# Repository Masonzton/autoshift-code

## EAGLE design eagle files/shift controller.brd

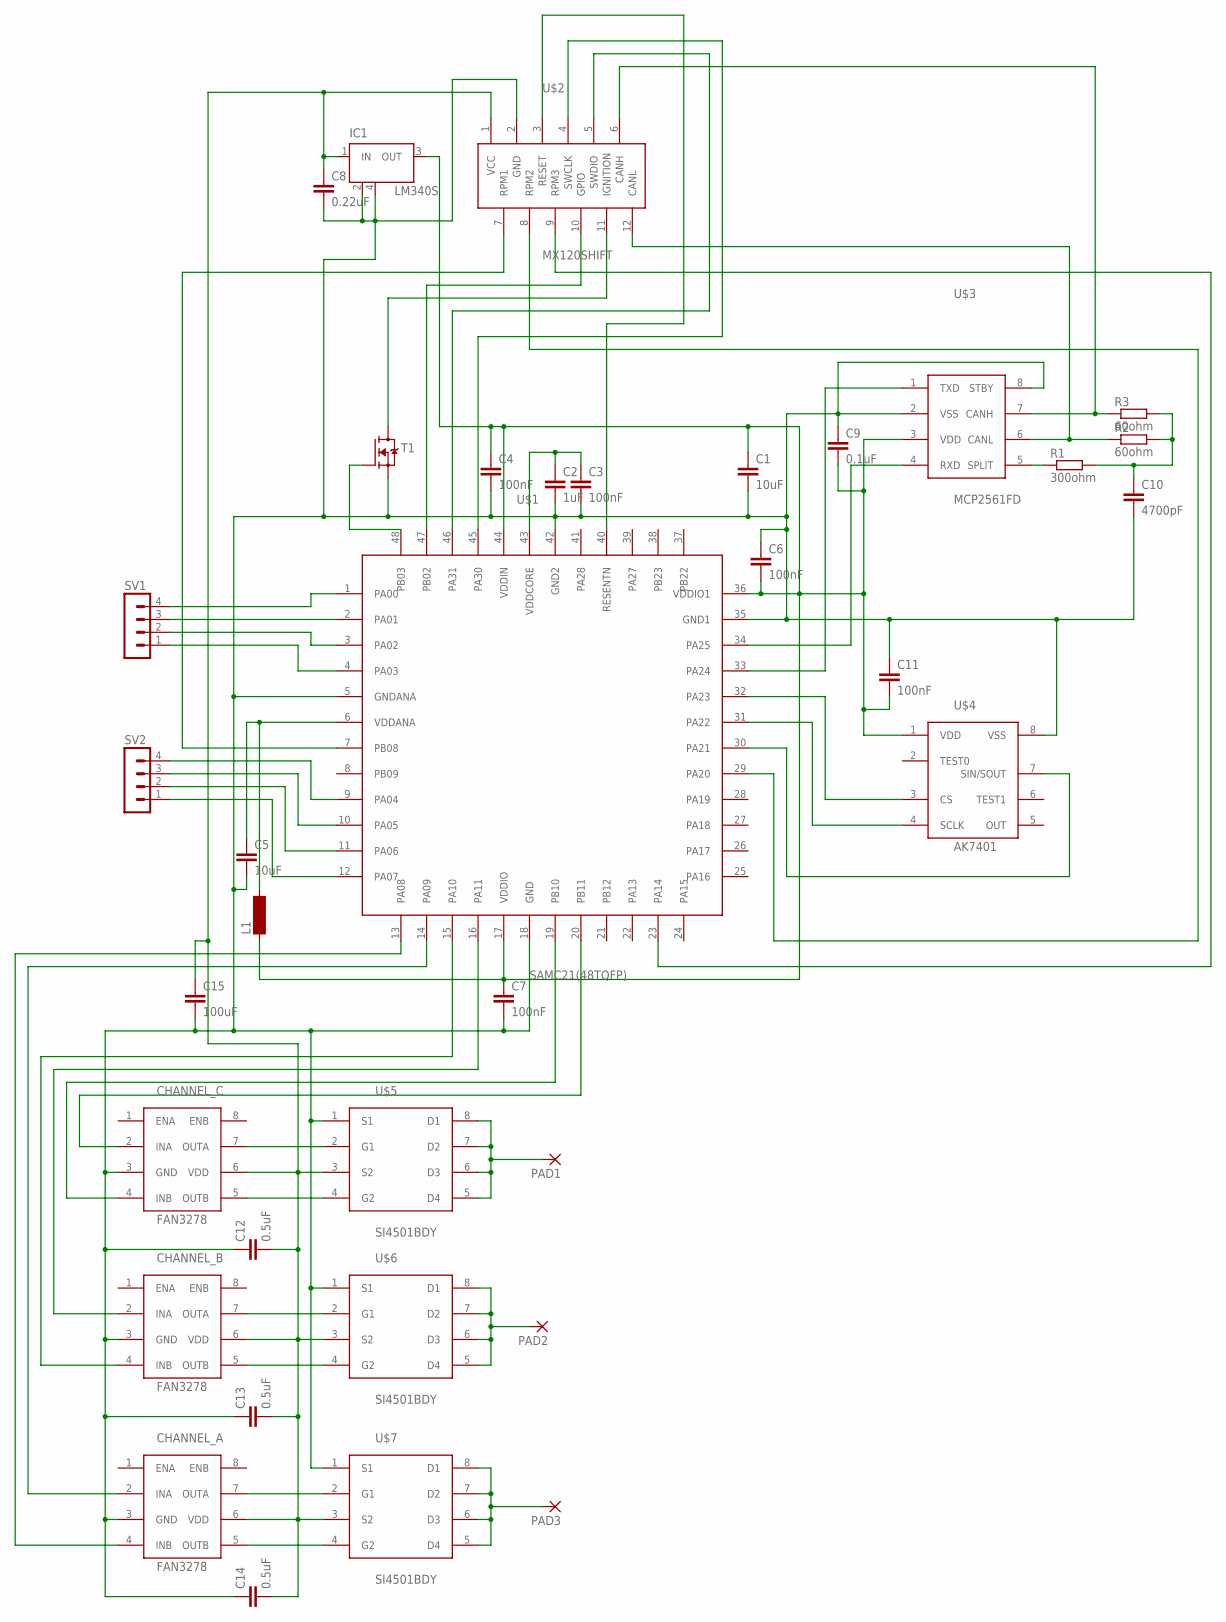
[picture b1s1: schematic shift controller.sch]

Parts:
C1, C5: 10uF; C1206
C2: 1uF; C1206
C3, C4, C6, C7, C11: 100nF; C1206
C8: 0.22uF; C1206
C9: 0.1uF; C1206
C10: 4700pF; C1206
C12, C13, C14: 0.5uF; C1206
C15: 100uF; C2.5-5
CHANNEL_A: FAN3278; SOIC-8
CHANNEL_B: FAN3278; SOIC-8
CHANNEL_C: FAN3278; SOIC-8
IC1: LM340S; SOT223
L1: SM-1206
PAD1, PAD2, PAD3: 3,81/1,4
R1: 300ohm; R1206
R2, R3: 60ohm; R1206
SV1, SV2: MA04-1
T1: MOSFET-N-SOT223; SOT223
U$1: SAMC21(48TQFP); TQFP-48
U$2: MX120SHIFT; 12X3.5PITCH
U$3: MCP2561FD; SOIC-8
U$4: AK7401; SOIC-8
U$5, U$6, U$7: SI4501BDY; SOIC-8

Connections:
unnamed: U$1.45 (PA30), U$2.4 (SWCLK)
unnamed: U$1.46 (PA31), U$2.5 (SWDIO)
unnamed: U$1.34 (PA25), U$3.4 (RXD)
unnamed: U$1.33 (PA24), U$3.1 (TXD)
unnamed: R3.1, U$2.6 (CANH), U$3.7 (CANH)
unnamed: R2.1, U$2.12 (CANL), U$3.6 (CANL)
unnamed: U$1.40 (RESENTN), U$2.3 (RESET)
unnamed: U$1.7 (PB08), U$2.7 (RPM1)
unnamed: U$1.23 (PA14), U$2.9 (RPM3)
unnamed: U$1.29 (PA20), U$2.8 (RPM2)
unnamed: SV1.4, U$1.1 (PA00)
unnamed: C8.1, C12.2, C13.2, C14.2, C15.1, CHANNEL_A.6 (VDD), CHANNEL_B.6 (VDD), CHANNEL_C.6 (VDD), IC1.1 (IN), U$2.1 (VCC), U$5.3 (S2), U$6.3 (S2), U$7.3 (S2)
unnamed: C1.1, C4.1, C6.2, C7.1, C9.2, C11.2, IC1.3 (OUT), L1.1, U$1.17 (VDDIO), U$1.36 (VDDIO1), U$1.44 (VDDIN), U$3.3 (VDD), U$4.1 (VDD)
unnamed: C2.1, C3.1, U$1.43 (VDDCORE)
unnamed: C5.1, L1.2, U$1.6 (VDDANA)
unnamed: R1.1, U$3.5 (SPLIT)
unnamed: C10.1, R1.2, R2.2, R3.2
unnamed: CHANNEL_C.2 (INA), U$1.20 (PB11)
unnamed: U$1.30 (PA21), U$4.7 (SIN/SOUT)
unnamed: U$1.31 (PA22), U$4.4 (SCLK)
unnamed: U$1.32 (PA23), U$4.3 (CS)
unnamed: T1.2 (D), T1.4 (D), U$2.11 (IGNITION)
unnamed: T1.1 (G), U$1.48 (PB03)
unnamed: PAD1.1, U$5.5 (D4), U$5.6 (D3), U$5.7 (D2), U$5.8 (D1)
unnamed: PAD2.1, U$6.5 (D4), U$6.6 (D3), U$6.7 (D2), U$6.8 (D1)
unnamed: PAD3.1, U$7.5 (D4), U$7.6 (D3), U$7.7 (D2), U$7.8 (D1)
unnamed: CHANNEL_C.4 (INB), U$1.19 (PB10)
unnamed: CHANNEL_C.7 (OUTA), U$5.2 (G1)
unnamed: CHANNEL_C.5 (OUTB), U$5.4 (G2)
unnamed: CHANNEL_B.7 (OUTA), U$6.2 (G1)
unnamed: CHANNEL_B.5 (OUTB), U$6.4 (G2)
unnamed: CHANNEL_A.7 (OUTA), U$7.2 (G1)
unnamed: CHANNEL_A.5 (OUTB), U$7.4 (G2)
unnamed: C1.2, C2.2, C3.2, C4.2, C5.2, C6.1, C7.2, C8.2, C9.1, C10.2, C11.1, C12.1, C13.1, C14.1, C15.2, CHANNEL_A.3 (GND), CHANNEL_B.3 (GND), CHANNEL_C.3 (GND), IC1.2 (GND), IC1.4 (GND), T1.3 (S), U$1.5 (GNDANA), U$1.18 (GND), U$1.35 (GND1), U$1.42 (GND2), U$2.2 (GND), U$3.2 (VSS), U$3.8 (STBY), U$4.8 (VSS), U$5.1 (S1), U$6.1 (S1), U$7.1 (S1)
unnamed: CHANNEL_B.2 (INA), U$1.16 (PA11)
unnamed: CHANNEL_B.4 (INB), U$1.15 (PA10)
unnamed: CHANNEL_A.2 (INA), U$1.14 (PA09)
unnamed: CHANNEL_A.4 (INB), U$1.13 (PA08)
unnamed: U$1.47 (PB02), U$2.10 (GPIO)
unnamed: SV1.3, U$1.2 (PA01)
unnamed: SV1.2, U$1.3 (PA02)
unnamed: SV1.1, U$1.4 (PA03)
unnamed: SV2.4, U$1.9 (PA04)
unnamed: SV2.3, U$1.10 (PA05)
unnamed: SV2.2, U$1.11 (PA06)
unnamed: SV2.1, U$1.12 (PA07)

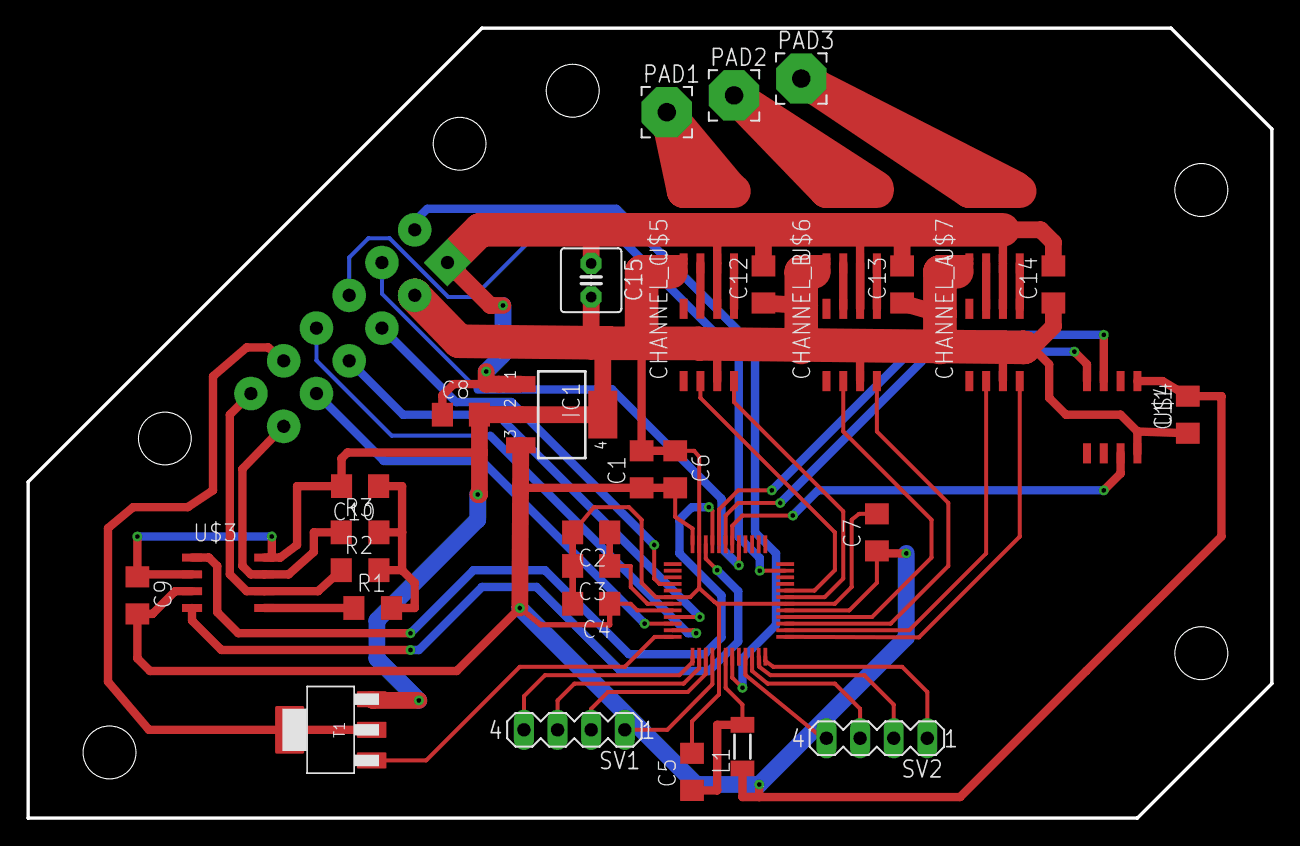
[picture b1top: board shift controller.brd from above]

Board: 2 copper layers, 94.0 x 59.7 mm, 36 parts (0 on the bottom side), 46 nets.

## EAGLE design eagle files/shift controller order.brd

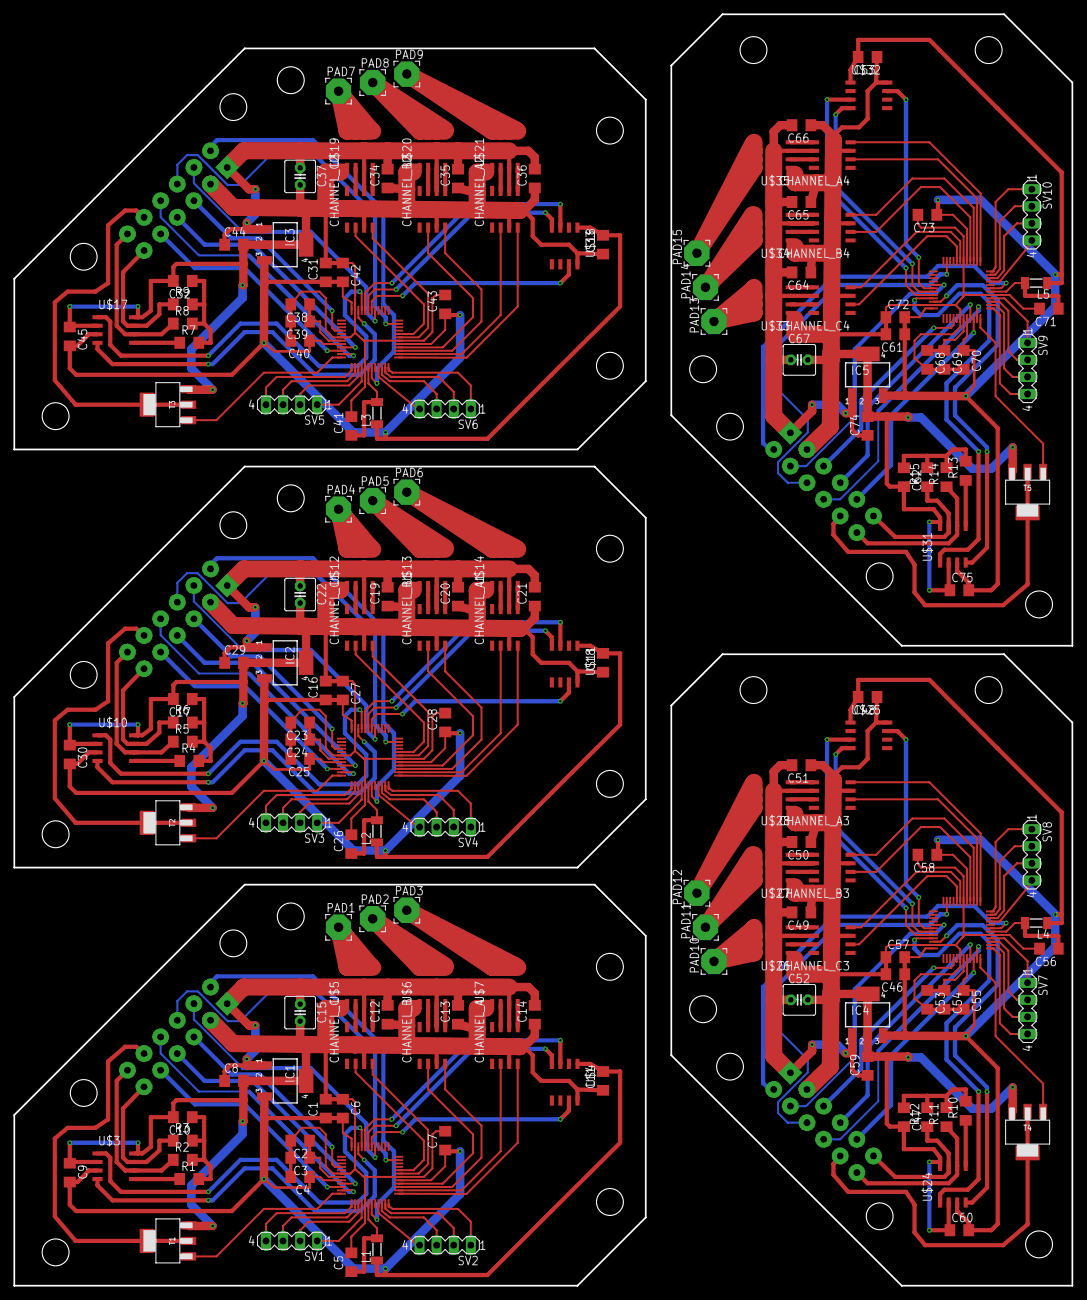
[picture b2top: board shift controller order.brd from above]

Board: 2 copper layers, 157.5 x 189.2 mm, 180 parts (0 on the bottom side), 230 nets.

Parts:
C1, C5, C16, C26, C31, C41, C46, C56, C61, C71: 10uF; C1206
C2, C23, C38, C53, C68: 1uF; C1206
C3, C4, C6, C7, C11, C18, C24, C25, C27, C28, C33, C39, C40, C42, C43, C48, C54, C55, C57, C58, C63, C69, C70, C72, C73: 100nF; C1206
C8, C29, C44, C59, C74: 0.22uF; C1206
C9, C30, C45, C60, C75: 0.1uF; C1206
C10, C17, C32, C47, C62: 4700pF; C1206
C12, C13, C14, C19, C20, C21, C34, C35, C36, C49, C50, C51, C64, C65, C66: 0.5uF; C1206
C15, C22, C37, C52, C67: 100uF; C2.5-5
CHANNEL_A, CHANNEL_A1, CHANNEL_A2, CHANNEL_A3, CHANNEL_A4: FAN3278; SOIC-8
CHANNEL_B, CHANNEL_B1, CHANNEL_B2, CHANNEL_B3, CHANNEL_B4: FAN3278; SOIC-8
CHANNEL_C, CHANNEL_C1, CHANNEL_C2, CHANNEL_C3, CHANNEL_C4: FAN3278; SOIC-8
IC1, IC2, IC3, IC4, IC5: LM340S; SOT223
L1, L2, L3, L4, L5: SM-1206
PAD1, PAD2, PAD3, PAD4, PAD5, PAD6, PAD7, PAD8, PAD9, PAD10, PAD11, PAD12, PAD13, PAD14, PAD15: 3,81/1,4
R1, R4, R7, R10, R13: 300ohm; R1206
R2, R3, R5, R6, R8, R9, R11, R12, R14, R15: 60ohm; R1206
SV1, SV2, SV3, SV4, SV5, SV6, SV7, SV8, SV9, SV10: MA04-1
T1, T2, T3, T4, T5: SOT223
U$1, U$8, U$15, U$22, U$29: SAMC21(48TQFP); TQFP-48
U$2, U$9, U$16, U$23, U$30: MX120SHIFT; 12X3.5PITCH
U$3, U$10, U$17, U$24, U$31: MCP2561FD; SOIC-8
U$4, U$11, U$18, U$25, U$32: AK7401; SOIC-8
U$5, U$6, U$7, U$12, U$13, U$14, U$19, U$20, U$21, U$26, U$27, U$28, U$33, U$34, U$35: SI4501BDY; SOIC-8

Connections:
unnamed: U$1.45, U$2.4
unnamed: U$1.46, U$2.5
unnamed: U$1.34, U$3.4
unnamed: U$1.33, U$3.1
unnamed: R3.1, U$2.6, U$3.7
unnamed: R2.1, U$2.12, U$3.6
unnamed: U$1.40, U$2.3
unnamed: U$1.7, U$2.7
unnamed: U$1.23, U$2.9
unnamed: U$1.29, U$2.8
unnamed: SV1.4, U$1.1
unnamed: C8.1, C12.2, C13.2, C14.2, C15.1, CHANNEL_A.6, CHANNEL_B.6, CHANNEL_C.6, IC1.1, U$2.1, U$5.3, U$6.3, U$7.3
unnamed: C1.1, C4.1, C6.2, C7.1, C9.2, C11.2, IC1.3, L1.1, U$1.17, U$1.36, U$1.44, U$3.3, U$4.1
unnamed: C2.1, C3.1, U$1.43
unnamed: C5.1, L1.2, U$1.6
unnamed: R1.1, U$3.5
unnamed: C10.1, R1.2, R2.2, R3.2
unnamed: CHANNEL_C.2, U$1.20
unnamed: U$1.30, U$4.7
unnamed: U$1.31, U$4.4
unnamed: U$1.32, U$4.3
unnamed: T1.2, T1.4, U$2.11
unnamed: T1.1, U$1.48
unnamed: PAD1.1, U$5.5, U$5.6, U$5.7, U$5.8
unnamed: PAD2.1, U$6.5, U$6.6, U$6.7, U$6.8
unnamed: PAD3.1, U$7.5, U$7.6, U$7.7, U$7.8
unnamed: CHANNEL_C.4, U$1.19
unnamed: CHANNEL_C.7, U$5.2
unnamed: CHANNEL_C.5, U$5.4
unnamed: CHANNEL_B.7, U$6.2
unnamed: CHANNEL_B.5, U$6.4
unnamed: CHANNEL_A.7, U$7.2
unnamed: CHANNEL_A.5, U$7.4
unnamed: C1.2, C2.2, C3.2, C4.2, C5.2, C6.1, C7.2, C8.2, C9.1, C10.2, C11.1, C12.1, C13.1, C14.1, C15.2, CHANNEL_A.3, CHANNEL_B.3, CHANNEL_C.3, IC1.2, IC1.4, T1.3, U$1.5, U$1.18, U$1.35, U$1.42, U$2.2, U$3.2, U$3.8, U$4.8, U$5.1, U$6.1, U$7.1
unnamed: CHANNEL_B.2, U$1.16
unnamed: CHANNEL_B.4, U$1.15
unnamed: CHANNEL_A.2, U$1.14
unnamed: CHANNEL_A.4, U$1.13
unnamed: U$1.47, U$2.10
unnamed: SV1.3, U$1.2
unnamed: SV1.2, U$1.3
unnamed: SV1.1, U$1.4
unnamed: SV2.4, U$1.9
unnamed: SV2.3, U$1.10
unnamed: SV2.2, U$1.11
unnamed: SV2.1, U$1.12
unnamed: U$8.45, U$9.4
unnamed: U$8.46, U$9.5
unnamed: U$8.33, U$10.1
unnamed: R6.1, U$9.6, U$10.7
unnamed: R5.1, U$9.12, U$10.6
unnamed: U$8.40, U$9.3
unnamed: C16.1, C18.2, C25.1, C27.2, C28.1, C30.2, IC2.3, L2.1, U$8.17, U$8.36, U$8.44, U$10.3, U$11.1
unnamed: C23.1, C24.1, U$8.43
unnamed: C26.1, L2.2, U$8.6
unnamed: U$8.34, U$10.4
unnamed: R4.1, U$10.5
unnamed: C17.1, R4.2, R5.2, R6.2
unnamed: U$8.30, U$11.7
unnamed: U$8.31, U$11.4
unnamed: U$8.32, U$11.3
unnamed: T2.2, T2.4, U$9.11
unnamed: T2.1, U$8.48
unnamed: PAD4.1, U$12.5, U$12.6, U$12.7, U$12.8
unnamed: PAD5.1, U$13.5, U$13.6, U$13.7, U$13.8
unnamed: PAD6.1, U$14.5, U$14.6, U$14.7, U$14.8
unnamed: C19.2, C20.2, C21.2, C22.1, C29.1, CHANNEL_A1.6, CHANNEL_B1.6, CHANNEL_C1.6, IC2.1, U$9.1, U$12.3, U$13.3, U$14.3
unnamed: CHANNEL_C1.7, U$12.2
unnamed: CHANNEL_C1.5, U$12.4
unnamed: CHANNEL_B1.7, U$13.2
unnamed: CHANNEL_B1.5, U$13.4
unnamed: CHANNEL_A1.7, U$14.2
unnamed: CHANNEL_A1.5, U$14.4
unnamed: CHANNEL_C1.2, U$8.20
unnamed: CHANNEL_C1.4, U$8.19
unnamed: CHANNEL_B1.2, U$8.16
unnamed: CHANNEL_B1.4, U$8.15
unnamed: CHANNEL_A1.2, U$8.14
unnamed: CHANNEL_A1.4, U$8.13
unnamed: U$8.7, U$9.7
unnamed: U$8.23, U$9.9
unnamed: U$8.29, U$9.8
unnamed: U$8.47, U$9.10
unnamed: SV3.4, U$8.1
unnamed: SV3.3, U$8.2
unnamed: SV3.2, U$8.3
unnamed: SV3.1, U$8.4
unnamed: SV4.4, U$8.9
unnamed: SV4.3, U$8.10
unnamed: SV4.2, U$8.11
unnamed: SV4.1, U$8.12
unnamed: C16.2, C17.2, C18.1, C19.1, C20.1, C21.1, C22.2, C23.2, C24.2, C25.2, C26.2, C27.1, C28.2, C29.2, C30.1, CHANNEL_A1.3, CHANNEL_B1.3, CHANNEL_C1.3, IC2.2, IC2.4, T2.3, U$8.5, U$8.18, U$8.35, U$8.42, U$9.2, U$10.2, U$10.8, U$11.8, U$12.1, U$13.1, U$14.1
unnamed: U$15.45, U$16.4
unnamed: U$15.46, U$16.5
unnamed: U$15.33, U$17.1
unnamed: R9.1, U$16.6, U$17.7
unnamed: R8.1, U$16.12, U$17.6
unnamed: U$15.40, U$16.3
unnamed: C31.1, C33.2, C40.1, C42.2, C43.1, C45.2, IC3.3, L3.1, U$15.17, U$15.36, U$15.44, U$17.3, U$18.1
unnamed: C38.1, C39.1, U$15.43
unnamed: C41.1, L3.2, U$15.6
unnamed: U$15.34, U$17.4
unnamed: R7.1, U$17.5
unnamed: C32.1, R7.2, R8.2, R9.2
unnamed: U$15.30, U$18.7
unnamed: U$15.31, U$18.4
unnamed: U$15.32, U$18.3
unnamed: T3.2, T3.4, U$16.11
unnamed: T3.1, U$15.48
unnamed: PAD7.1, U$19.5, U$19.6, U$19.7, U$19.8
unnamed: PAD8.1, U$20.5, U$20.6, U$20.7, U$20.8
unnamed: PAD9.1, U$21.5, U$21.6, U$21.7, U$21.8
unnamed: C34.2, C35.2, C36.2, C37.1, C44.1, CHANNEL_A2.6, CHANNEL_B2.6, CHANNEL_C2.6, IC3.1, U$16.1, U$19.3, U$20.3, U$21.3
unnamed: CHANNEL_C2.7, U$19.2
unnamed: CHANNEL_C2.5, U$19.4
unnamed: CHANNEL_B2.7, U$20.2
unnamed: CHANNEL_B2.5, U$20.4
unnamed: CHANNEL_A2.7, U$21.2
unnamed: CHANNEL_A2.5, U$21.4
unnamed: CHANNEL_C2.2, U$15.20
unnamed: CHANNEL_C2.4, U$15.19
unnamed: CHANNEL_B2.2, U$15.16
unnamed: CHANNEL_B2.4, U$15.15
unnamed: CHANNEL_A2.2, U$15.14
unnamed: CHANNEL_A2.4, U$15.13
unnamed: U$15.7, U$16.7
unnamed: U$15.23, U$16.9
unnamed: U$15.29, U$16.8
unnamed: U$15.47, U$16.10
unnamed: SV5.4, U$15.1
unnamed: SV5.3, U$15.2
unnamed: SV5.2, U$15.3
unnamed: SV5.1, U$15.4
unnamed: SV6.4, U$15.9
unnamed: SV6.3, U$15.10
unnamed: SV6.2, U$15.11
unnamed: SV6.1, U$15.12
unnamed: C31.2, C32.2, C33.1, C34.1, C35.1, C36.1, C37.2, C38.2, C39.2, C40.2, C41.2, C42.1, C43.2, C44.2, C45.1, CHANNEL_A2.3, CHANNEL_B2.3, CHANNEL_C2.3, IC3.2, IC3.4, T3.3, U$15.5, U$15.18, U$15.35, U$15.42, U$16.2, U$17.2, U$17.8, U$18.8, U$19.1, U$20.1, U$21.1
unnamed: U$22.45, U$23.4
unnamed: U$22.46, U$23.5
unnamed: U$22.33, U$24.1
unnamed: R12.1, U$23.6, U$24.7
unnamed: R11.1, U$23.12, U$24.6
unnamed: U$22.40, U$23.3
unnamed: C46.1, C48.2, C55.1, C57.2, C58.1, C60.2, IC4.3, L4.1, U$22.17, U$22.36, U$22.44, U$24.3, U$25.1
unnamed: C53.1, C54.1, U$22.43
unnamed: C56.1, L4.2, U$22.6
unnamed: U$22.34, U$24.4
unnamed: R10.1, U$24.5
unnamed: C47.1, R10.2, R11.2, R12.2
unnamed: U$22.30, U$25.7
unnamed: U$22.31, U$25.4
unnamed: U$22.32, U$25.3
unnamed: T4.2, T4.4, U$23.11
unnamed: T4.1, U$22.48
unnamed: PAD10.1, U$26.5, U$26.6, U$26.7, U$26.8
unnamed: PAD11.1, U$27.5, U$27.6, U$27.7, U$27.8
unnamed: PAD12.1, U$28.5, U$28.6, U$28.7, U$28.8
unnamed: C49.2, C50.2, C51.2, C52.1, C59.1, CHANNEL_A3.6, CHANNEL_B3.6, CHANNEL_C3.6, IC4.1, U$23.1, U$26.3, U$27.3, U$28.3
unnamed: CHANNEL_C3.7, U$26.2
unnamed: CHANNEL_C3.5, U$26.4
unnamed: CHANNEL_B3.7, U$27.2
unnamed: CHANNEL_B3.5, U$27.4
unnamed: CHANNEL_A3.7, U$28.2
unnamed: CHANNEL_A3.5, U$28.4
unnamed: CHANNEL_C3.2, U$22.20
unnamed: CHANNEL_C3.4, U$22.19
unnamed: CHANNEL_B3.2, U$22.16
unnamed: CHANNEL_B3.4, U$22.15
unnamed: CHANNEL_A3.2, U$22.14
unnamed: CHANNEL_A3.4, U$22.13
unnamed: U$22.7, U$23.7
unnamed: U$22.23, U$23.9
unnamed: U$22.29, U$23.8
unnamed: U$22.47, U$23.10
unnamed: SV7.4, U$22.1
unnamed: SV7.3, U$22.2
unnamed: SV7.2, U$22.3
unnamed: SV7.1, U$22.4
unnamed: SV8.4, U$22.9
unnamed: SV8.3, U$22.10
unnamed: SV8.2, U$22.11
unnamed: SV8.1, U$22.12
unnamed: C46.2, C47.2, C48.1, C49.1, C50.1, C51.1, C52.2, C53.2, C54.2, C55.2, C56.2, C57.1, C58.2, C59.2, C60.1, CHANNEL_A3.3, CHANNEL_B3.3, CHANNEL_C3.3, IC4.2, IC4.4, T4.3, U$22.5, U$22.18, U$22.35, U$22.42, U$23.2, U$24.2, U$24.8, U$25.8, U$26.1, U$27.1, U$28.1
unnamed: U$29.45, U$30.4
unnamed: U$29.46, U$30.5
unnamed: U$29.33, U$31.1
unnamed: R15.1, U$30.6, U$31.7
unnamed: R14.1, U$30.12, U$31.6
unnamed: U$29.40, U$30.3
unnamed: C61.1, C63.2, C70.1, C72.2, C73.1, C75.2, IC5.3, L5.1, U$29.17, U$29.36, U$29.44, U$31.3, U$32.1
unnamed: C68.1, C69.1, U$29.43
unnamed: C71.1, L5.2, U$29.6
unnamed: U$29.34, U$31.4
unnamed: R13.1, U$31.5
unnamed: C62.1, R13.2, R14.2, R15.2
unnamed: U$29.30, U$32.7
unnamed: U$29.31, U$32.4
unnamed: U$29.32, U$32.3
unnamed: T5.2, T5.4, U$30.11
unnamed: T5.1, U$29.48
unnamed: PAD13.1, U$33.5, U$33.6, U$33.7, U$33.8
unnamed: PAD14.1, U$34.5, U$34.6, U$34.7, U$34.8
unnamed: PAD15.1, U$35.5, U$35.6, U$35.7, U$35.8
unnamed: C64.2, C65.2, C66.2, C67.1, C74.1, CHANNEL_A4.6, CHANNEL_B4.6, CHANNEL_C4.6, IC5.1, U$30.1, U$33.3, U$34.3, U$35.3
unnamed: CHANNEL_C4.7, U$33.2
unnamed: CHANNEL_C4.5, U$33.4
unnamed: CHANNEL_B4.7, U$34.2
unnamed: CHANNEL_B4.5, U$34.4
unnamed: CHANNEL_A4.7, U$35.2
unnamed: CHANNEL_A4.5, U$35.4
unnamed: CHANNEL_C4.2, U$29.20
unnamed: CHANNEL_C4.4, U$29.19
unnamed: CHANNEL_B4.2, U$29.16
unnamed: CHANNEL_B4.4, U$29.15
unnamed: CHANNEL_A4.2, U$29.14
unnamed: CHANNEL_A4.4, U$29.13
unnamed: U$29.7, U$30.7
unnamed: U$29.23, U$30.9
unnamed: U$29.29, U$30.8
unnamed: U$29.47, U$30.10
unnamed: SV9.4, U$29.1
unnamed: SV9.3, U$29.2
unnamed: SV9.2, U$29.3
unnamed: SV9.1, U$29.4
unnamed: SV10.4, U$29.9
unnamed: SV10.3, U$29.10
unnamed: SV10.2, U$29.11
unnamed: SV10.1, U$29.12
unnamed: C61.2, C62.2, C63.1, C64.1, C65.1, C66.1, C67.2, C68.2, C69.2, C70.2, C71.2, C72.1, C73.2, C74.2, C75.1, CHANNEL_A4.3, CHANNEL_B4.3, CHANNEL_C4.3, IC5.2, IC5.4, T5.3, U$29.5, U$29.18, U$29.35, U$29.42, U$30.2, U$31.2, U$31.8, U$32.8, U$33.1, U$34.1, U$35.1

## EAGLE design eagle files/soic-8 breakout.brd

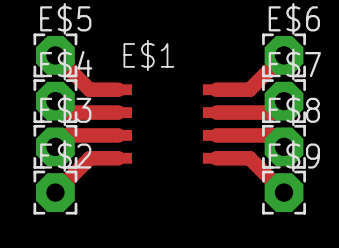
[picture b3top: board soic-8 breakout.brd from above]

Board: 2 copper layers, 9 parts (0 on the bottom side), 8 nets.

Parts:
E$1: SOIC-8
E$2, E$3, E$4, E$5, E$6, E$7, E$8, E$9: 2,15/1,0

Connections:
S$1: E$1.1, E$5.1
S$4: E$1.2, E$4.1
S$5: E$1.3, E$3.1
S$6: E$1.4, E$2.1
S$7: E$1.5, E$9.1
S$8: E$1.6, E$8.1
S$9: E$1.7, E$7.1
S$10: E$1.8, E$6.1

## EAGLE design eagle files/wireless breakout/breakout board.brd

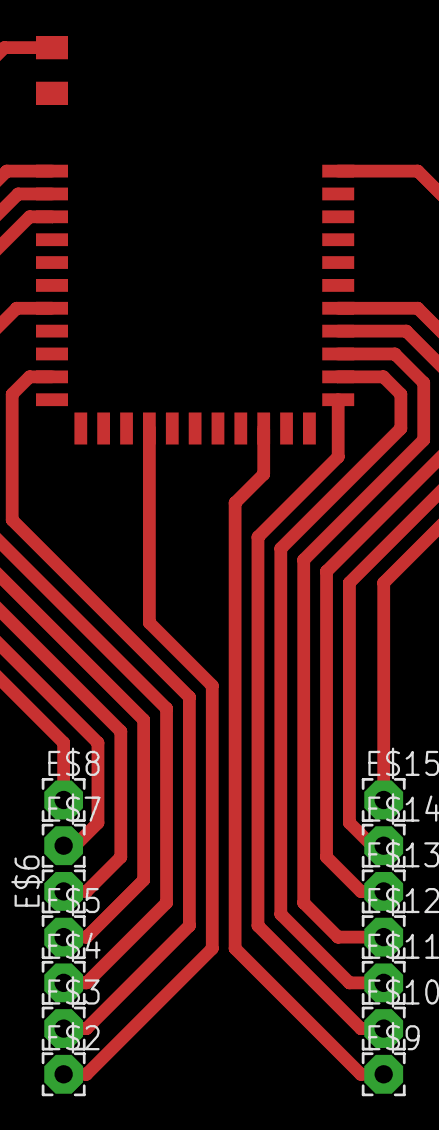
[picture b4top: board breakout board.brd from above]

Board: 2 copper layers, 15 parts (0 on the bottom side), 14 nets.

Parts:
E$1: WIRELESS-CAS
E$2, E$3, E$4, E$5, E$6, E$7, E$8, E$9, E$10, E$11, E$12, E$13, E$14, E$15: 2,15/1,0

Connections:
S$1: E$1.1, E$8.1
S$2: E$1.3, E$7.1
S$3: E$1.4, E$6.1
S$4: E$1.5, E$5.1
S$6: E$1.9, E$4.1
S$7: E$1.17, E$2.1
S$8: E$1.22, E$9.1
S$9: E$1.25, E$10.1
S$10: E$1.26, E$11.1
S$11: E$1.27, E$12.1
S$12: E$1.28, E$13.1
S$13: E$1.29, E$14.1
S$14: E$1.35, E$15.1
S$15: E$1.12, E$3.1

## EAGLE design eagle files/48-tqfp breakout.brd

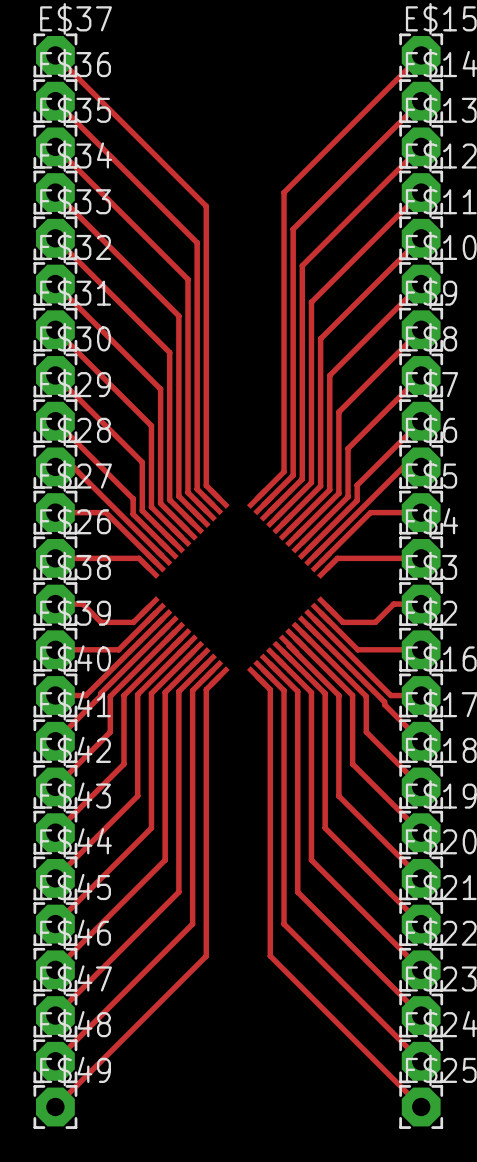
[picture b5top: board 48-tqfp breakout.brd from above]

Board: 2 copper layers, 49 parts (0 on the bottom side), 48 nets.

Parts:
E$1: TQFP-48
E$2, E$3, E$4, E$5, E$6, E$7, E$8, E$9, E$10, E$11, E$12, E$13, E$14, E$15, E$16, E$17, E$18, E$19, E$20, E$21, E$22, E$23, E$24, E$25, E$26, E$27, E$28, E$29, E$30, E$31, E$32, E$33, E$34, E$35, E$36, E$37, E$38, E$39, E$40, E$41, E$42, E$43, E$44, E$45, E$46, E$47, E$48, E$49: 2,15/1,0

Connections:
S$1: E$1.24, E$49.1
S$2: E$1.23, E$48.1
S$3: E$1.22, E$47.1
S$4: E$1.21, E$46.1
S$5: E$1.20, E$45.1
S$6: E$1.19, E$44.1
S$7: E$1.18, E$43.1
S$8: E$1.17, E$42.1
S$9: E$1.16, E$41.1
S$10: E$1.15, E$40.1
S$11: E$1.14, E$39.1
S$12: E$1.13, E$38.1
S$13: E$1.12, E$26.1
S$14: E$1.11, E$27.1
S$15: E$1.10, E$28.1
S$16: E$1.9, E$29.1
S$17: E$1.8, E$30.1
S$18: E$1.7, E$31.1
S$19: E$1.6, E$32.1
S$20: E$1.5, E$33.1
S$21: E$1.4, E$34.1
S$22: E$1.3, E$35.1
S$23: E$1.2, E$36.1
S$24: E$1.1, E$37.1
S$25: E$1.25, E$25.1
S$26: E$1.26, E$24.1
S$27: E$1.27, E$23.1
S$28: E$1.28, E$22.1
S$29: E$1.29, E$21.1
S$30: E$1.30, E$20.1
S$31: E$1.31, E$19.1
S$32: E$1.32, E$18.1
S$33: E$1.33, E$17.1
S$34: E$1.34, E$16.1
S$35: E$1.35, E$2.1
S$36: E$1.36, E$3.1
S$37: E$1.37, E$4.1
S$38: E$1.38, E$5.1
S$39: E$1.39, E$6.1
S$40: E$1.40, E$7.1
S$41: E$1.41, E$8.1
S$42: E$1.42, E$9.1
S$43: E$1.43, E$10.1
S$44: E$1.44, E$11.1
S$45: E$1.45, E$12.1
S$46: E$1.46, E$13.1
S$47: E$1.47, E$14.1
S$48: E$1.48, E$15.1

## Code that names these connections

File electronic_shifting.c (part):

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

//PORTA pins (high side bridge) //digital pins
#define H1 PIN_PA08
#define H2 PIN_PA10
#define H3 PIN_PB10

#define CONF_PWM_MODULE      TCC0
#define CONF_PWM_CHANNEL     3 //this number is equal to W0=3 pin
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#define L3_OUTPUT 5

//encoder digital pins
#define CS PIN_PA23
#define CLOCK PIN_PA22
#define DATA PIN_PA21

//ignition cut digital pin
#define IGNCUT PIN_PB03

//shift button digital pins
//#define SHIFT_UP 18
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
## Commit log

2018-12-22 initial codes
2018-12-22 due non-volitile upload
2018-12-22 Create tachometer.py
    Reads COM6 for rpm sensor data. Right now set to read print
2018-12-22 debug
2018-12-22 gui update for mac compatability
2018-12-23 simulink display demo
2019-01-03 shift board
2019-01-03 eagle libraries
2019-01-04 shift board update
2019-01-13 sam micro update
2019-01-13 sam update
2019-01-13 sam try 2
2019-01-13 library update
2019-01-13 board update
2019-01-13 board cam
2019-02-03 controller schematic updates
2019-02-05 created function to change pwm values
    need delay_init in order to use delay.
2019-02-14 create can.c
    this still doesn't work. I think that there is a problem with either the can code or the wiring.
2019-02-14 board stuff
2019-03-05 attempt at converting arduino to sam electronic shifting
    ? what does the power represent in Timer set pwmDuty
    still need to test every macro and setup
    still need to add setup to main
    need to add can macros
2019-03-05 debug can
    used this file to debug the can bus
    still need to figure out sending comprehensible messages. Theory that it has something to do with baud rates because can_set_baudrate changes the messages.
